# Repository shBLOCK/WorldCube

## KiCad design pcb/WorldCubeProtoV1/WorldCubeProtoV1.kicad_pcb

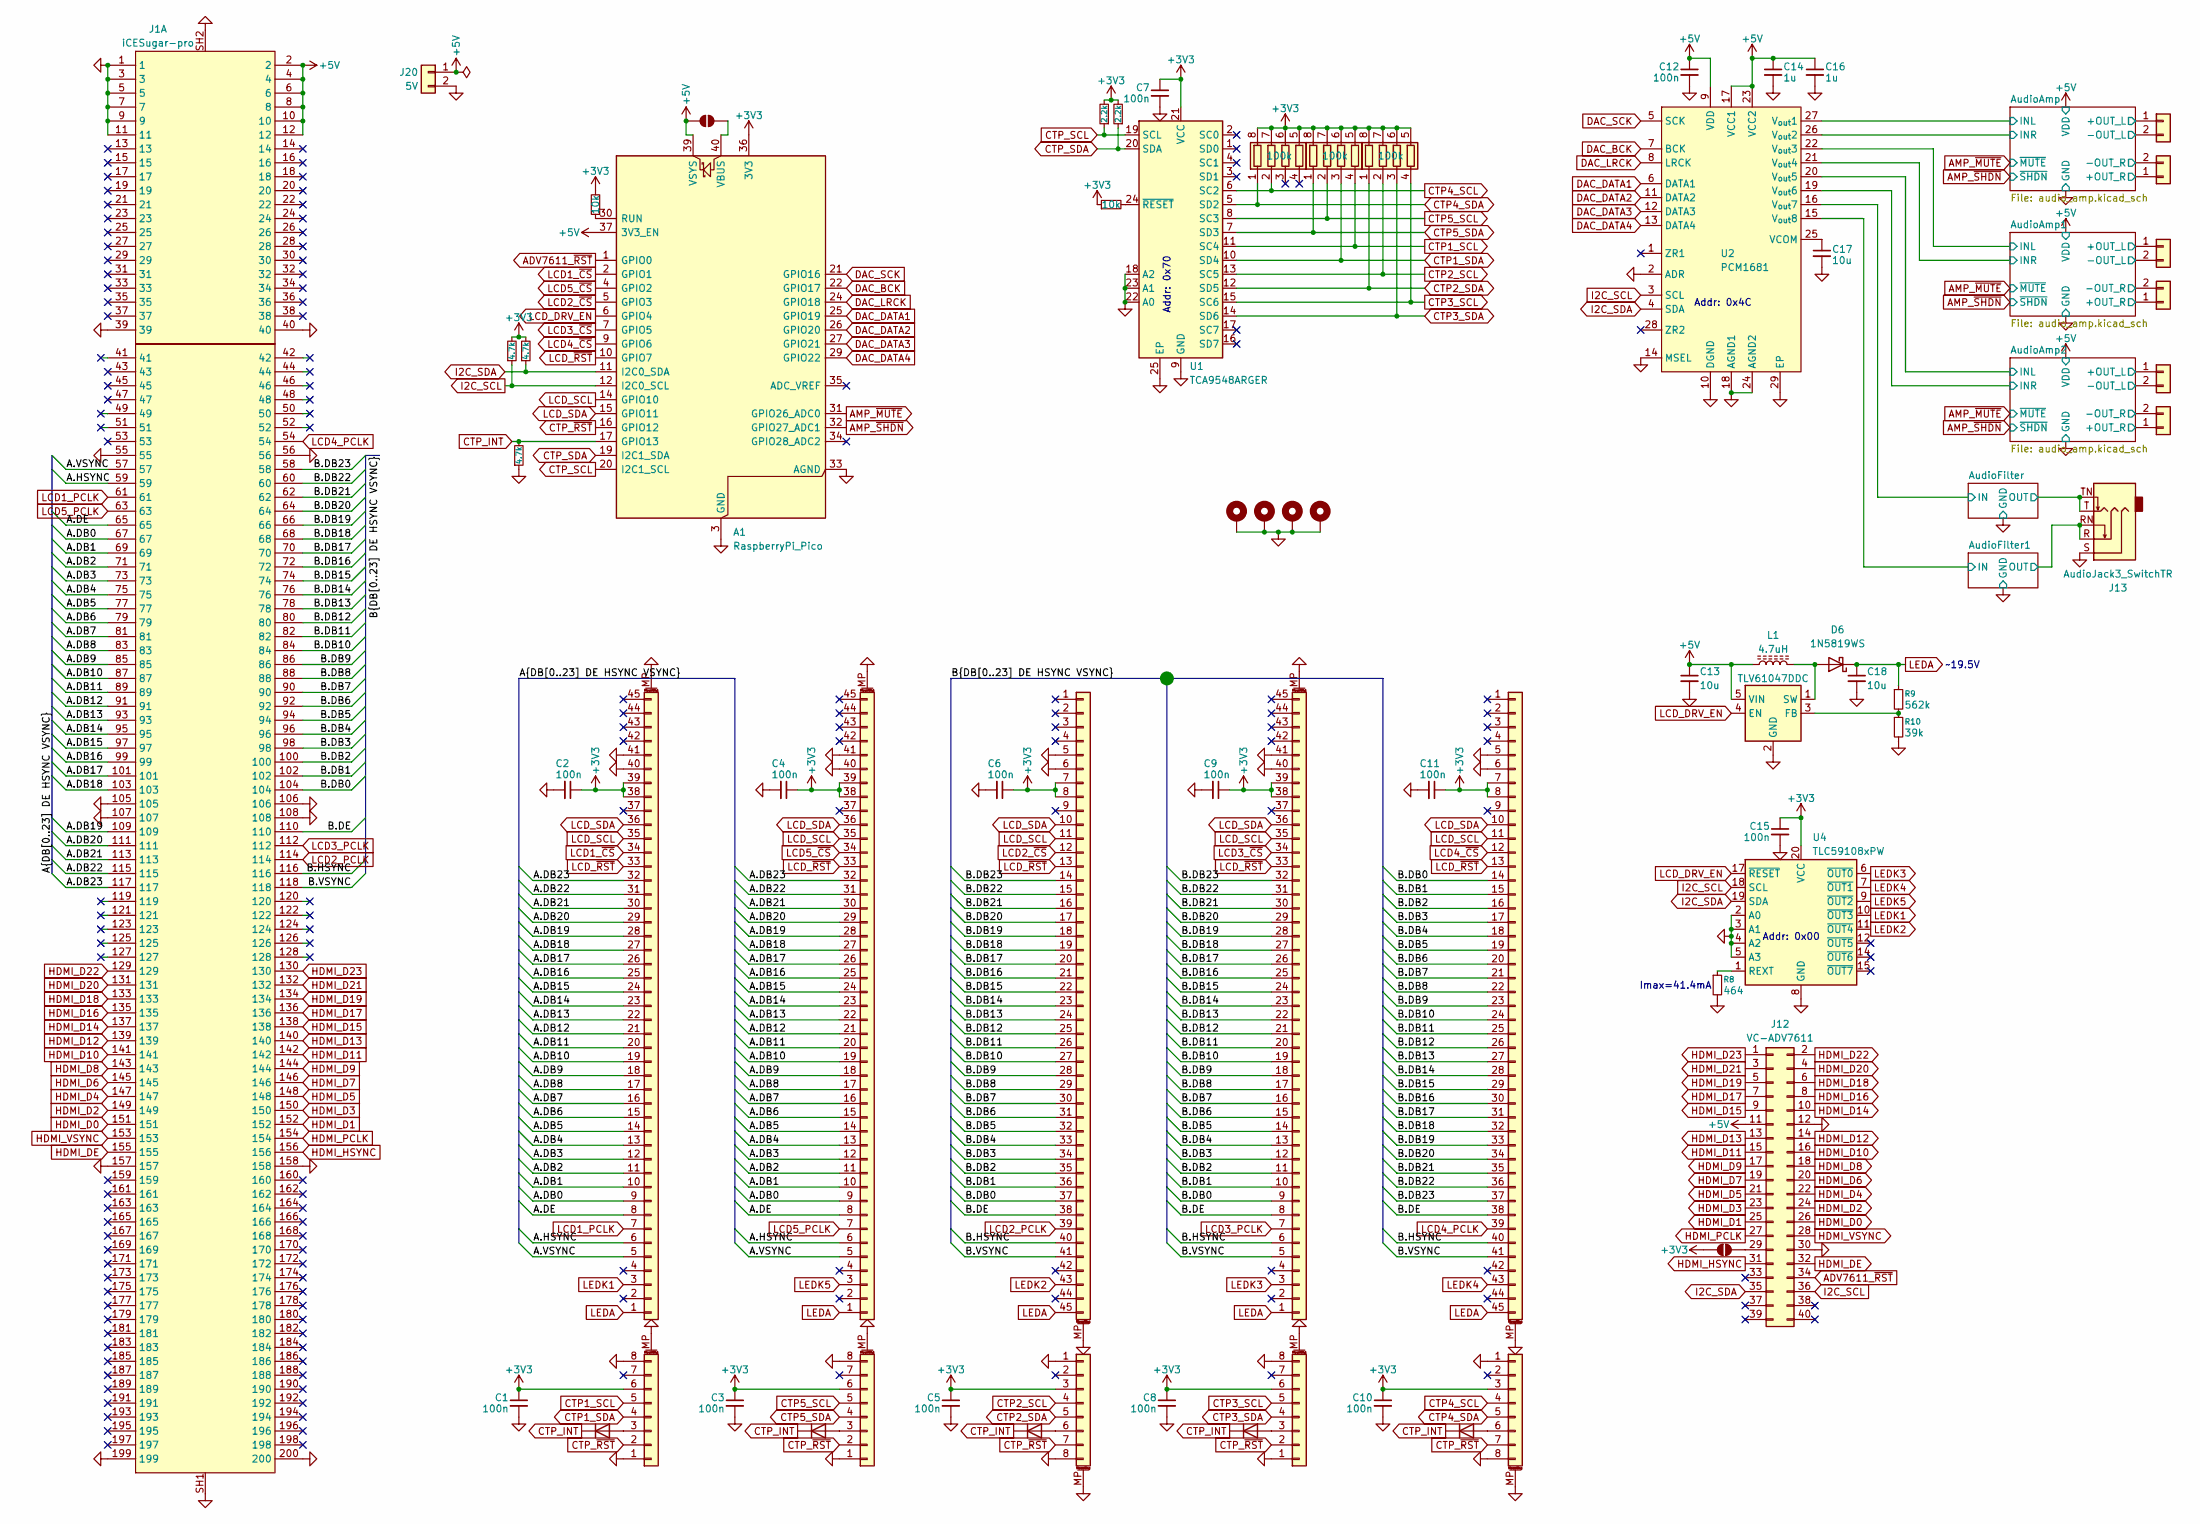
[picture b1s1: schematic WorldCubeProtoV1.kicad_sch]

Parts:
A1: RaspberryPi_Pico; RaspberryPi_Pico_Common_SMD; LCSC C42924268
C1, C2, C3, C4, C5, C6, C7, C8, C9, C10, C11, C12, C15: 100n; C_0603_1608Metric; LCSC C14663
C13, C18: 10u; C_0805_2012Metric; LCSC C2932476
C14, C16: 1u; C_0603_1608Metric; LCSC C15849
C17: 10u; C_0603_1608Metric; LCSC C19702
D1, D2, D3, D4, D5: 1N4148WT; D_SOD-523; LCSC C7420320
D6: 1N5819WS; D_SOD-323; LCSC C191023
H1, H2, H3, H4: MountingHole_Pad; MountingHole_3.2mm_M3_Pad
J1: iCESugar-pro; TE_1565917-4; LCSC C279171
J2, J4, J8: KD040WXFPD014; TE_4-1734839-5_1x45-1MP_P0.5mm_Horizontal; LCSC C53058
J3, J5, J9: KD040WXFPD014-C015C_CTP; TE_0-1734839-8_1x08-1MP_P0.5mm_Horizontal; LCSC C262555
J6, J10: KD040WXFPD014; TE_4-1734839-5_1x45-1MP_P0.5mm_Horizontal; LCSC C262649
J7, J11: KD040WXFPD014-C015C_CTP; TE_0-1734839-8_1x08-1MP_P0.5mm_Horizontal; LCSC C262581
J12: VC-ADV7611; PinHeader_2x20_P2.54mm_Vertical; LCSC C5224014
J13: AudioJack3_SwitchTR; Jack_3.5mm_CUI_SJ1-3515N_Horizontal; LCSC C145814
J14, J15, J16, J17, J18, J19: Conn_01x02; Molex_PicoBlade_53047-0210_1x02_P1.25mm_Vertical; LCSC C7430458
J20: 5V; JST_XH_B2B-XH-A_1x02_P2.50mm_Vertical; LCSC C158012
JP1, JP2: SolderJumper_2_Open; SolderJumper-2_P1.3mm_Open_RoundedPad1.0x1.5mm
L1: 4.7uH; L_Changjiang_FTC252010S; LCSC C5832360
R1, R6: 10k; R_0603_1608Metric; LCSC C25804
R2, R3, R4: 4.7k; R_0603_1608Metric; LCSC C23162
R5, R7: 2.2k; R_0603_1608Metric; LCSC C4190
R8: 464; R_0603_1608Metric; LCSC C5159701
R9: 562k; R_0603_1608Metric; LCSC C23205
R10: 39k; R_0603_1608Metric; LCSC C23153
RN1, RN2, RN3: 100k; R_Array_Convex_4x0603; LCSC C192933
U1: TCA9548ARGER; Texas_RGE0024C_VQFN-24-1EP_4x4mm_P0.5mm_EP2.1x2.1mm; LCSC C555456
U2: PCM1681; HTSSOP-28-1EP_4.4x9.7mm_P0.65mm_EP3.4x9.5mm_Mask2.4x6.17mm; LCSC C2667052
U3: TLV61047DDC; SOT-23-5; LCSC C44538408
U4: TLC59108xPW; TSSOP-20_4.4x6.5mm_P0.65mm; LCSC C130031

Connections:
+3V3: A1.36 (3V3), C1.1, C2.1, C3.1, C4.1, C5.1, C6.1, C7.1, C8.1, C9.1, C10.1, C11.1, C15.1, J2.38, J2.39, J3.6, J4.38, J4.39, J5.6, J6.7, J6.8, J7.3, J8.38, J8.39, J9.6, J10.7, J10.8, J11.3, JP2.1 (A), R1.2, R2.2, R3.2, R5.2, R6.1, R7.2, RN1.5 (R4.2), RN1.6 (R3.2), RN1.7 (R2.2), RN1.8 (R1.2), RN2.5 (R4.2), RN2.6 (R3.2), RN2.7 (R2.2), RN2.8 (R1.2), RN3.5 (R4.2), RN3.6 (R3.2), RN3.7 (R2.2), RN3.8 (R1.2), U1.21 (VCC), U4.20 (VCC)
+5V: A1.37 (3V3_EN), A1.39 (VSYS), C12.1, C13.1, C14.1, C16.1, J1.2, J1.4, J1.6, J1.8, J1.10, J1.12, J12.11, J20.1, JP1.1 (A), L1.1, U2.9 (VDD), U2.17 (VCC1), U2.23 (VCC2), U3.5 (VIN); also elsewhere on the board
/A.DB0: J1.67, J2.9, J4.9
/A.DB1: J1.69, J2.10, J4.10
/A.DB2: J1.71, J2.11, J4.11
/A.DB3: J1.73, J2.12, J4.12
/A.DB4: J1.75, J2.13, J4.13
/A.DB5: J1.77, J2.14, J4.14
/A.DB6: J1.79, J2.15, J4.15
/A.DB7: J1.81, J2.16, J4.16
/A.DB8: J1.83, J2.17, J4.17
/A.DB9: J1.85, J2.18, J4.18
/A.DB10: J1.87, J2.19, J4.19
/A.DB11: J1.89, J2.20, J4.20
/A.DB12: J1.91, J2.21, J4.21
/A.DB13: J1.93, J2.22, J4.22
/A.DB14: J1.95, J2.23, J4.23
/A.DB15: J1.97, J2.24, J4.24
/A.DB16: J1.99, J2.25, J4.25
/A.DB17: J1.101, J2.26, J4.26
/A.DB18: J1.103, J2.27, J4.27
/A.DB19: J1.109, J2.28, J4.28
/A.DB20: J1.111, J2.29, J4.29
/A.DB21: J1.113, J2.30, J4.30
/A.DB22: J1.115, J2.31, J4.31
/A.DB23: J1.117, J2.32, J4.32
/A.DE: J1.65, J2.8, J4.8
/A.HSYNC: J1.59, J2.6, J4.6
/A.VSYNC: J1.57, J2.5, J4.5
/AudioAmp1/+OUT_L: J16.1; also elsewhere on the board
/AudioAmp1/+OUT_R: J17.1; also elsewhere on the board
/AudioAmp1/-OUT_L: J16.2; also elsewhere on the board
/AudioAmp1/-OUT_R: J17.2; also elsewhere on the board
/AudioAmp1/INL: U2.22 (V_{out}3); also elsewhere on the board
/AudioAmp1/INR: U2.21 (V_{out}4); also elsewhere on the board
/AudioAmp2/+OUT_L: J18.1; also elsewhere on the board
/AudioAmp2/+OUT_R: J19.1; also elsewhere on the board
/AudioAmp2/-OUT_L: J18.2; also elsewhere on the board
/AudioAmp2/-OUT_R: J19.2; also elsewhere on the board
/AudioAmp2/INL: U2.20 (V_{out}5); also elsewhere on the board
/AudioAmp2/INR: U2.19 (V_{out}6); also elsewhere on the board
/AudioAmp/+OUT_L: J14.1; also elsewhere on the board
/AudioAmp/+OUT_R: J15.1; also elsewhere on the board
/AudioAmp/-OUT_L: J14.2; also elsewhere on the board
/AudioAmp/-OUT_R: J15.2; also elsewhere on the board
/AudioAmp/INL: U2.27 (V_{out}1); also elsewhere on the board
/AudioAmp/INR: U2.26 (V_{out}2); also elsewhere on the board
/AudioFilter1/IN: U2.15 (V_{out}8); also elsewhere on the board
/AudioFilter1/OUT: J13.R, J13.RN; also elsewhere on the board
/AudioFilter/IN: U2.16 (V_{out}7); also elsewhere on the board
/AudioFilter/OUT: J13.T, J13.TN; also elsewhere on the board
/B.DB0: J1.104, J6.37, J8.9, J10.14
/B.DB1: J1.102, J6.36, J8.10, J10.15
/B.DB2: J1.100, J6.35, J8.11, J10.16
/B.DB3: J1.98, J6.34, J8.12, J10.17
/B.DB4: J1.96, J6.33, J8.13, J10.18
/B.DB5: J1.94, J6.32, J8.14, J10.19
/B.DB6: J1.92, J6.31, J8.15, J10.20
/B.DB7: J1.90, J6.30, J8.16, J10.21
/B.DB8: J1.88, J6.29, J8.17, J10.22
/B.DB9: J1.86, J6.28, J8.18, J10.23
/B.DB10: J1.84, J6.27, J8.19, J10.24
/B.DB11: J1.82, J6.26, J8.20, J10.25
/B.DB12: J1.80, J6.25, J8.21, J10.26
/B.DB13: J1.78, J6.24, J8.22, J10.27
/B.DB14: J1.76, J6.23, J8.23, J10.28
/B.DB15: J1.74, J6.22, J8.24, J10.29
/B.DB16: J1.72, J6.21, J8.25, J10.30
/B.DB17: J1.70, J6.20, J8.26, J10.31
/B.DB18: J1.68, J6.19, J8.27, J10.32
/B.DB19: J1.66, J6.18, J8.28, J10.33
/B.DB20: J1.64, J6.17, J8.29, J10.34
/B.DB21: J1.62, J6.16, J8.30, J10.35
/B.DB22: J1.60, J6.15, J8.31, J10.36
/B.DB23: J1.58, J6.14, J8.32, J10.37
/B.DE: J1.110, J6.38, J8.8, J10.38
/B.HSYNC: J1.116, J6.40, J8.6, J10.40
/B.VSYNC: J1.118, J6.41, J8.5, J10.41
ADV7611_~RST: A1.1 (GPIO0), J12.34
AMP_~MUTE: A1.31 (GPIO26_ADC0); also elsewhere on the board
AMP_~SHDN: A1.32 (GPIO27_ADC1); also elsewhere on the board
CTP1_SCL: J3.5, RN2.4 (R4.1), U1.11 (SC4)
CTP1_SDA: J3.4, RN2.3 (R3.1), U1.10 (SD4)
CTP2_SCL: J7.4, RN3.2 (R2.1), U1.13 (SC5)
CTP2_SDA: J7.5, RN3.1 (R1.1), U1.12 (SD5)
CTP3_SCL: J9.5, RN3.4 (R4.1), U1.15 (SC6)
CTP3_SDA: J9.4, RN3.3 (R3.1), U1.14 (SD6)
CTP4_SCL: J11.4, RN1.2 (R2.1), U1.6 (SC2)
CTP4_SDA: J11.5, RN1.1 (R1.1), U1.5 (SD2)
CTP5_SCL: J5.5, RN2.2 (R2.1), U1.8 (SC3)
CTP5_SDA: J5.4, RN2.1 (R1.1), U1.7 (SD3)
CTP_INT: A1.17 (GPIO13), D1.1 (K), D2.1 (K), D3.1 (K), D4.1 (K), D5.1 (K), R4.2
CTP_SCL: A1.20 (I2C1_SCL), R5.1, U1.19 (SCL)
CTP_SDA: A1.19 (I2C1_SDA), R7.1, U1.20 (SDA)
CTP_~RST: A1.16 (GPIO12), J3.2, J5.2, J7.7, J9.2, J11.7
DAC_BCK: A1.22 (GPIO17), U2.7 (BCK)
DAC_DATA1: A1.25 (GPIO19), U2.6 (DATA1)
DAC_DATA2: A1.26 (GPIO20), U2.11 (DATA2)
DAC_DATA3: A1.27 (GPIO21), U2.12 (DATA3)
DAC_DATA4: A1.29 (GPIO22), U2.13 (DATA4)
DAC_LRCK: A1.24 (GPIO18), U2.8 (LRCK)
DAC_SCK: A1.21 (GPIO16), U2.5 (SCK)
GND: A1.3 (GND), A1.8 (GND), A1.13 (GND), A1.18 (GND), A1.23 (GND), A1.28 (GND), A1.33 (AGND), A1.38 (GND), C1.2, C2.2, C3.2, C4.2, C5.2, C6.2, C7.2, C8.2, C9.2, C10.2, C11.2, C12.2, C13.2, C14.2, C15.2, C16.2, C17.2, C18.2, H1.1, H2.1, H3.1, H4.1, J1.1, J1.3, J1.5, J1.7, J1.9, J1.11, J1.39, J1.40, J1.55, J1.56, J1.105, J1.106, J1.107, J1.108, J1.157, J1.158, J1.199, J1.200, J1.SH1, J1.SH2, J2.40, J2.41, J2.MP (MountPin), J3.1, J3.8, J3.MP (MountPin), J4.40, J4.41, J4.MP (MountPin), J5.1, J5.8, J5.MP (MountPin), J6.5, J6.6, J6.MP (MountPin), J7.1, J7.8, J7.MP (MountPin), J8.40, J8.41, J8.MP (MountPin), J9.1, J9.8, J9.MP (MountPin), J10.5, J10.6, J10.MP (MountPin), J11.1, J11.8, J11.MP (MountPin), J12.12, J12.30, J13.S, J20.2, R4.1, R8.2, R10.2, U1.9 (GND), U1.18 (A2), U1.22 (A0), U1.23 (A1), U1.25 (EP), U2.2 (ADR), U2.10 (DGND), U2.14 (MSEL), U2.18 (AGND1), U2.24 (AGND2), U2.29 (EP), U3.2 (GND), U4.2 (A0), U4.3 (A1), U4.4 (A2), U4.5 (A3), U4.8 (GND), U4.13 (GND), U4.16 (GND); also elsewhere on the board
HDMI_D0: J1.151, J12.26
HDMI_D1: J1.152, J12.25
HDMI_D2: J1.149, J12.24
HDMI_D3: J1.150, J12.23
HDMI_D4: J1.147, J12.22
HDMI_D5: J1.148, J12.21
HDMI_D6: J1.145, J12.20
HDMI_D7: J1.146, J12.19
HDMI_D8: J1.143, J12.18
HDMI_D9: J1.144, J12.17
HDMI_D10: J1.141, J12.16
HDMI_D11: J1.142, J12.15
HDMI_D12: J1.139, J12.14
HDMI_D13: J1.140, J12.13
HDMI_D14: J1.137, J12.10
HDMI_D15: J1.138, J12.9
HDMI_D16: J1.135, J12.8
HDMI_D17: J1.136, J12.7
HDMI_D18: J1.133, J12.6
HDMI_D19: J1.134, J12.5
HDMI_D20: J1.131, J12.4
HDMI_D21: J1.132, J12.3
HDMI_D22: J1.129, J12.2
HDMI_D23: J1.130, J12.1
HDMI_DE: J1.155, J12.32
HDMI_HSYNC: J1.156, J12.31
HDMI_PCLK: J1.154, J12.27
HDMI_VSYNC: J1.153, J12.28
I2C_SCL: A1.12 (I2C0_SCL), J12.36, R3.1, U2.3 (SCL), U4.18 (SCL)
I2C_SDA: A1.11 (I2C0_SDA), J12.35, R2.1, U2.4 (SDA), U4.19 (SDA)
LCD1_PCLK: J1.61, J2.7
LCD1_~CS: A1.2 (GPIO1), J2.34
LCD2_PCLK: J1.114, J6.39
LCD2_~CS: A1.5 (GPIO3), J6.12
LCD3_PCLK: J1.112, J8.7
LCD3_~CS: A1.7 (GPIO5), J8.34
LCD4_PCLK: J1.54, J10.39
LCD4_~CS: A1.9 (GPIO6), J10.12
LCD5_PCLK: J1.63, J4.7
LCD5_~CS: A1.4 (GPIO2), J4.34
LCD_DRV_EN: A1.6 (GPIO4), U3.4 (EN), U4.17 (~RESET)
LCD_SCL: A1.14 (GPIO10), J2.35, J4.35, J6.11, J8.35, J10.11
LCD_SDA: A1.15 (GPIO11), J2.36, J4.36, J6.10, J8.36, J10.10
LCD_~RST: A1.10 (GPIO7), J2.33, J4.33, J6.13, J8.33, J10.13
LEDA: C18.1, D6.1 (K), J2.1, J4.1, J6.45, J8.1, J10.45, R9.1
LEDK1: J2.3, U4.10 (~OUT3)
LEDK2: J6.43, U4.11 (~OUT4)
LEDK3: J8.3, U4.6 (~OUT0)
LEDK4: J10.43, U4.7 (~OUT1)
LEDK5: J4.3, U4.9 (~OUT2)
unnamed: A1.30 (RUN), R1.1
unnamed: A1.40 (VBUS), JP1.2 (B)
unnamed: D1.2 (A), J3.3
unnamed: D2.2 (A), J5.3
unnamed: D3.2 (A), J7.6
unnamed: D4.2 (A), J9.3
unnamed: D5.2 (A), J11.6
unnamed: D6.2 (A), L1.2, U3.1 (SW)
unnamed: J12.29, JP2.2 (B)
unnamed: R6.2, U1.24 (~RESET)
unnamed: C17.1, U2.25 (VCOM)
unnamed: R9.2, R10.1, U3.3 (FB)
unnamed: R8.1, U4.1 (REXT)

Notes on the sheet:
Addr: 0x4C
Imax=41.4mA
Addr: 0x70
Addr: 0x00
~19.5V

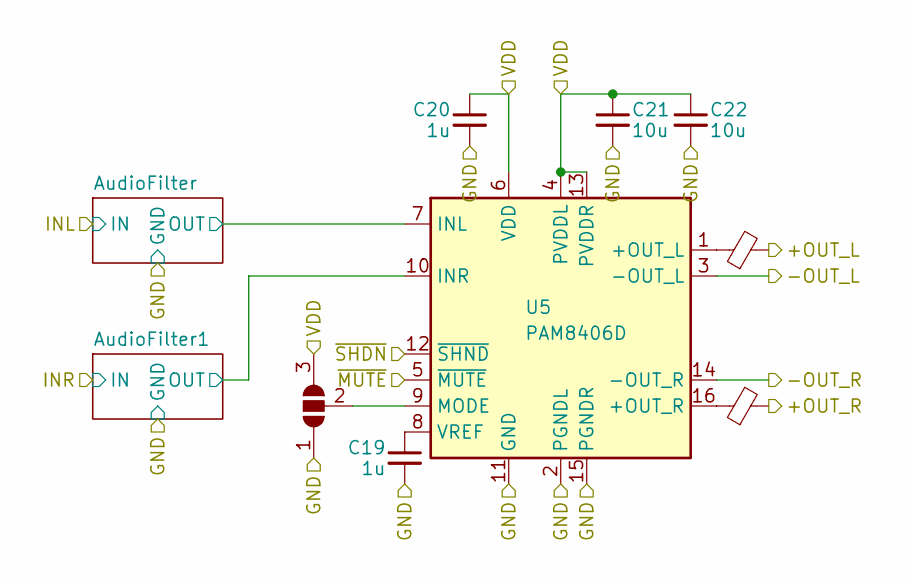
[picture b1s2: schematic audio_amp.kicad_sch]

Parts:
C19, C20: 1u; C_0603_1608Metric; LCSC C15849
C21, C22: 10u; C_0603_1608Metric; LCSC C19702
FB1, FB2: BLM21PG221SN1D; L_0805_2012Metric; LCSC C85840
JP3: AMP_MODE; SolderJumper-3_P1.3mm_Open_RoundedPad1.0x1.5mm
U5: PAM8406D; SOIC-16_3.9x9.9mm_P1.27mm; LCSC C86270

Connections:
+5V: C20.1, C21.1, C22.1, JP3.3 (B), U5.4 (PVDDL), U5.6 (VDD), U5.13 (PVDDR); also elsewhere on the board
/AudioAmp/+OUT_L: FB1.2; also elsewhere on the board
/AudioAmp/+OUT_R: FB2.2; also elsewhere on the board
/AudioAmp/-OUT_L: U5.3 (-OUT_L); also elsewhere on the board
/AudioAmp/-OUT_R: U5.14 (-OUT_R); also elsewhere on the board
/AudioAmp/AudioFilter1/OUT: U5.10 (INR); also elsewhere on the board
/AudioAmp/AudioFilter/OUT: U5.7 (INL); also elsewhere on the board
AMP_~MUTE: U5.5 (~MUTE); also elsewhere on the board
AMP_~SHDN: U5.12 (~SHND); also elsewhere on the board
GND: C19.2, C20.2, C21.2, C22.2, JP3.1 (A), U5.2 (PGNDL), U5.11 (GND), U5.15 (PGNDR); also elsewhere on the board
unnamed: JP3.2 (C), U5.9 (MODE)
unnamed: FB1.1, U5.1 (+OUT_L)
unnamed: FB2.1, U5.16 (+OUT_R)
unnamed: C19.1, U5.8 (VREF)

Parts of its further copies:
C23, C24, C27, C28: 1u; C_0603_1608Metric; LCSC C15849
C25, C26, C29, C30: 10u; C_0603_1608Metric; LCSC C19702
FB3, FB4, FB5, FB6: BLM21PG221SN1D; L_0805_2012Metric; LCSC C85840
JP4, JP5: AMP_MODE; SolderJumper-3_P1.3mm_Open_RoundedPad1.0x1.5mm
U6, U7: PAM8406D; SOIC-16_3.9x9.9mm_P1.27mm; LCSC C86270

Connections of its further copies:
+5V: C24.1, C25.1, C26.1, C28.1, C29.1, C30.1, JP4.3 (B), JP5.3 (B), U6.4 (PVDDL), U6.6 (VDD), U6.13 (PVDDR), U7.4 (PVDDL), U7.6 (VDD), U7.13 (PVDDR); also elsewhere on the board
/AudioAmp1/+OUT_L: FB3.2; also elsewhere on the board
/AudioAmp1/+OUT_R: FB4.2; also elsewhere on the board
/AudioAmp1/-OUT_L: U6.3 (-OUT_L); also elsewhere on the board
/AudioAmp1/-OUT_R: U6.14 (-OUT_R); also elsewhere on the board
/AudioAmp1/AudioFilter1/OUT: U6.10 (INR); also elsewhere on the board
/AudioAmp1/AudioFilter/OUT: U6.7 (INL); also elsewhere on the board
/AudioAmp2/+OUT_L: FB5.2; also elsewhere on the board
/AudioAmp2/+OUT_R: FB6.2; also elsewhere on the board
/AudioAmp2/-OUT_L: U7.3 (-OUT_L); also elsewhere on the board
/AudioAmp2/-OUT_R: U7.14 (-OUT_R); also elsewhere on the board
/AudioAmp2/AudioFilter1/OUT: U7.10 (INR); also elsewhere on the board
/AudioAmp2/AudioFilter/OUT: U7.7 (INL); also elsewhere on the board
AMP_~MUTE: U6.5 (~MUTE), U7.5 (~MUTE); also elsewhere on the board
AMP_~SHDN: U6.12 (~SHND), U7.12 (~SHND); also elsewhere on the board
GND: C23.2, C24.2, C25.2, C26.2, C27.2, C28.2, C29.2, C30.2, JP4.1 (A), JP5.1 (A), U6.2 (PGNDL), U6.11 (GND), U6.15 (PGNDR), U7.2 (PGNDL), U7.11 (GND), U7.15 (PGNDR); also elsewhere on the board
unnamed: JP4.2 (C), U6.9 (MODE)
unnamed: JP5.2 (C), U7.9 (MODE)
unnamed: FB3.1, U6.1 (+OUT_L)
unnamed: FB4.1, U6.16 (+OUT_R)
unnamed: C23.1, U6.8 (VREF)
unnamed: FB5.1, U7.1 (+OUT_L)
unnamed: FB6.1, U7.16 (+OUT_R)
unnamed: C27.1, U7.8 (VREF)

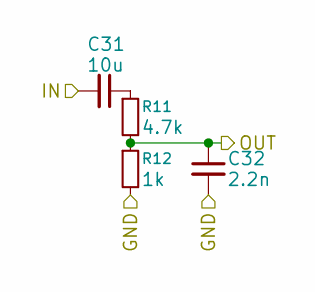
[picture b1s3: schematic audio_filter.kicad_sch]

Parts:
C31: 10u; C_0603_1608Metric; LCSC C19702
C32: 2.2n; C_0603_1608Metric; LCSC C1604
R11: 4.7k; R_0603_1608Metric; LCSC C23162
R12: 1k; R_0603_1608Metric; LCSC C21190

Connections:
/AudioAmp/AudioFilter/OUT: C32.1, R11.2, R12.1; also elsewhere on the board
/AudioAmp/INL: C31.2; also elsewhere on the board
GND: C32.2, R12.2; also elsewhere on the board
unnamed: C31.1, R11.1

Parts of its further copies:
C33, C35, C37, C39, C41, C43, C45: 10u; C_0603_1608Metric; LCSC C19702
C34, C36, C38, C40, C42, C44, C46: 2.2n; C_0603_1608Metric; LCSC C1604
R13, R15, R17, R19, R21, R23, R25: 4.7k; R_0603_1608Metric; LCSC C23162
R14, R16, R18, R20, R22, R24, R26: 1k; R_0603_1608Metric; LCSC C21190

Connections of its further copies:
/AudioAmp1/AudioFilter1/OUT: C40.1, R19.2, R20.1; also elsewhere on the board
/AudioAmp1/AudioFilter/OUT: C34.1, R13.2, R14.1; also elsewhere on the board
/AudioAmp1/INL: C33.2; also elsewhere on the board
/AudioAmp1/INR: C39.2; also elsewhere on the board
/AudioAmp2/AudioFilter1/OUT: C42.1, R21.2, R22.1; also elsewhere on the board
/AudioAmp2/AudioFilter/OUT: C36.1, R15.2, R16.1; also elsewhere on the board
/AudioAmp2/INL: C35.2; also elsewhere on the board
/AudioAmp2/INR: C41.2; also elsewhere on the board
/AudioAmp/AudioFilter1/OUT: C38.1, R17.2, R18.1; also elsewhere on the board
/AudioAmp/INR: C37.2; also elsewhere on the board
/AudioFilter1/IN: C45.2; also elsewhere on the board
/AudioFilter1/OUT: C46.1, R25.2, R26.1; also elsewhere on the board
/AudioFilter/IN: C43.2; also elsewhere on the board
/AudioFilter/OUT: C44.1, R23.2, R24.1; also elsewhere on the board
GND: C34.2, C36.2, C38.2, C40.2, C42.2, C44.2, C46.2, R14.2, R16.2, R18.2, R20.2, R22.2, R24.2, R26.2; also elsewhere on the board
unnamed: C33.1, R13.1
unnamed: C35.1, R15.1
unnamed: C37.1, R17.1
unnamed: C39.1, R19.1
unnamed: C41.1, R21.1
unnamed: C43.1, R23.1
unnamed: C45.1, R25.1

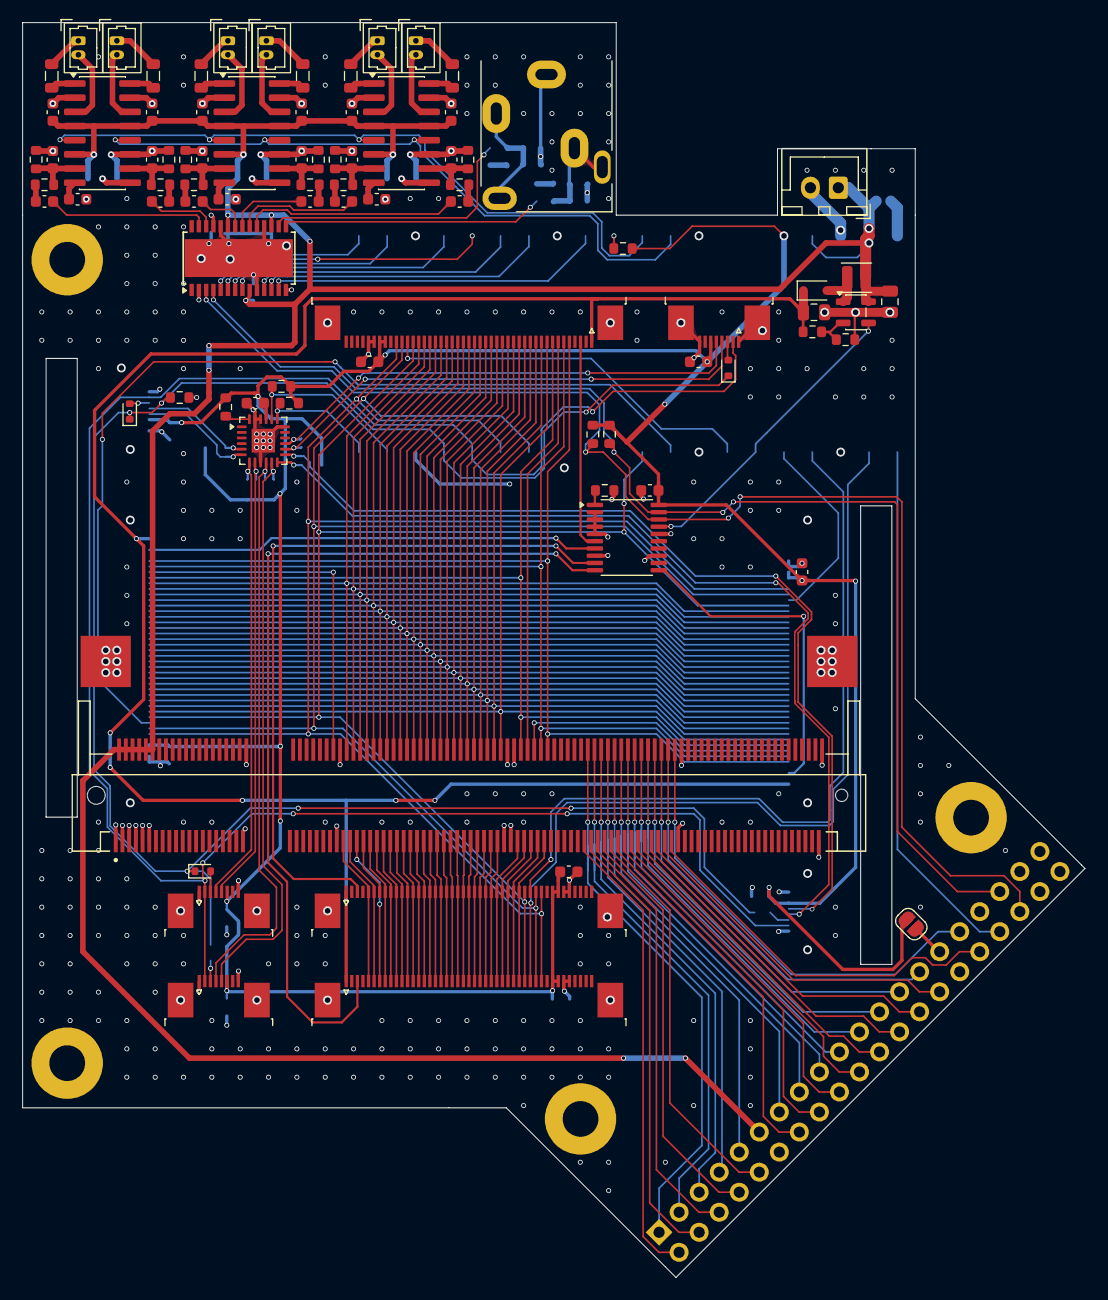
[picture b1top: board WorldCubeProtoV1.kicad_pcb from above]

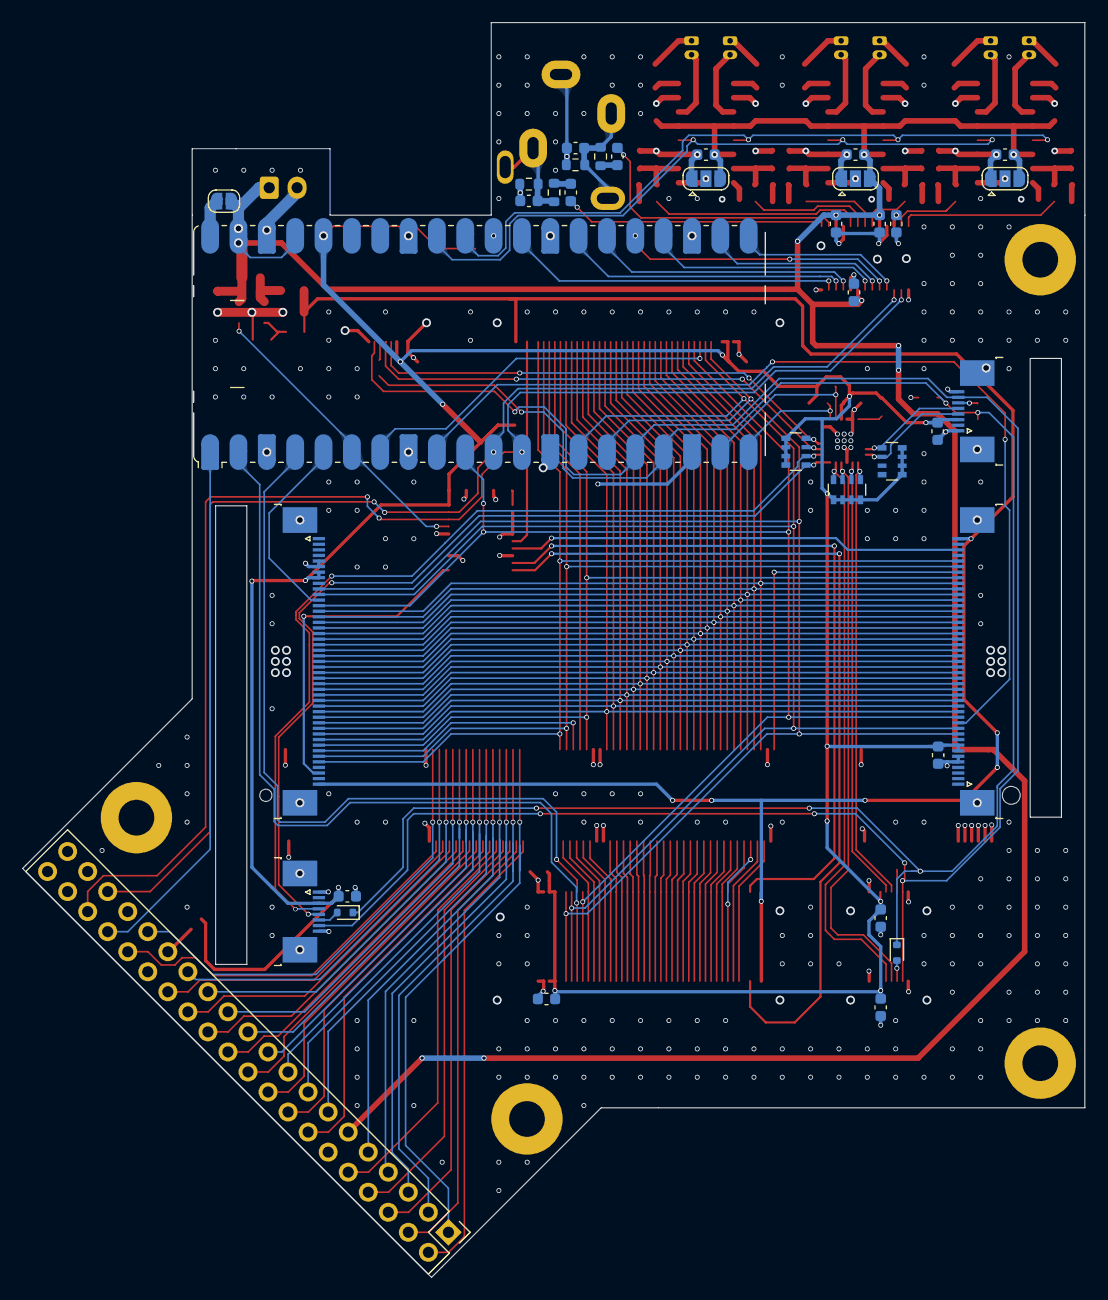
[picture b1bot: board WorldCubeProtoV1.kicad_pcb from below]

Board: 4 copper layers, 95.2 x 112.5 mm, 125 parts (36 on the bottom side), 192 nets.

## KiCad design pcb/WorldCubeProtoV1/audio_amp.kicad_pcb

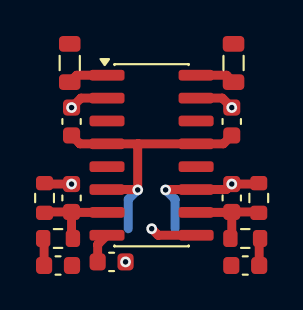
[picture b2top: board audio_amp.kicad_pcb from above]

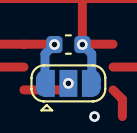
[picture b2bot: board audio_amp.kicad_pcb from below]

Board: 2 copper layers, 16 parts (2 on the bottom side), 10 nets.

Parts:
C1, C2: 1u; C_0603_1608Metric
C3, C4, C5, C7: 10u; C_0603_1608Metric
C6, C8: 2.2n; C_0603_1608Metric
FB1, FB2: BLM21PG221SN1D; L_0805_2012Metric
JP1: AMP_MODE; SolderJumper-3_P1.3mm_Open_RoundedPad1.0x1.5mm
R1, R3: 4.7k; R_0603_1608Metric
R2, R4: 1k; R_0603_1608Metric
U1: PAM8406D; SOIC-16_3.9x9.9mm_P1.27mm

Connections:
/AudioFilter1/OUT: C8.1, R3.2, R4.1, U1.10 (INR)
/AudioFilter/OUT: C6.1, R1.2, R2.1, U1.7 (INL)
/GND: C1.2, C2.2, C3.2, C4.2, C6.2, C8.2, JP1.1 (A), R2.2, R4.2, U1.2 (PGNDL), U1.11 (GND), U1.15 (PGNDR)
/VDD: C2.1, C3.1, C4.1, JP1.3 (B), U1.4 (PVDDL), U1.6 (VDD), U1.13 (PVDDR)
unnamed: C5.1, R1.1
unnamed: C7.1, R3.1
unnamed: JP1.2 (C), U1.9 (MODE)
unnamed: FB1.1, U1.1 (+OUT_L)
unnamed: FB2.1, U1.16 (+OUT_R)
unnamed: C1.1, U1.8 (VREF)

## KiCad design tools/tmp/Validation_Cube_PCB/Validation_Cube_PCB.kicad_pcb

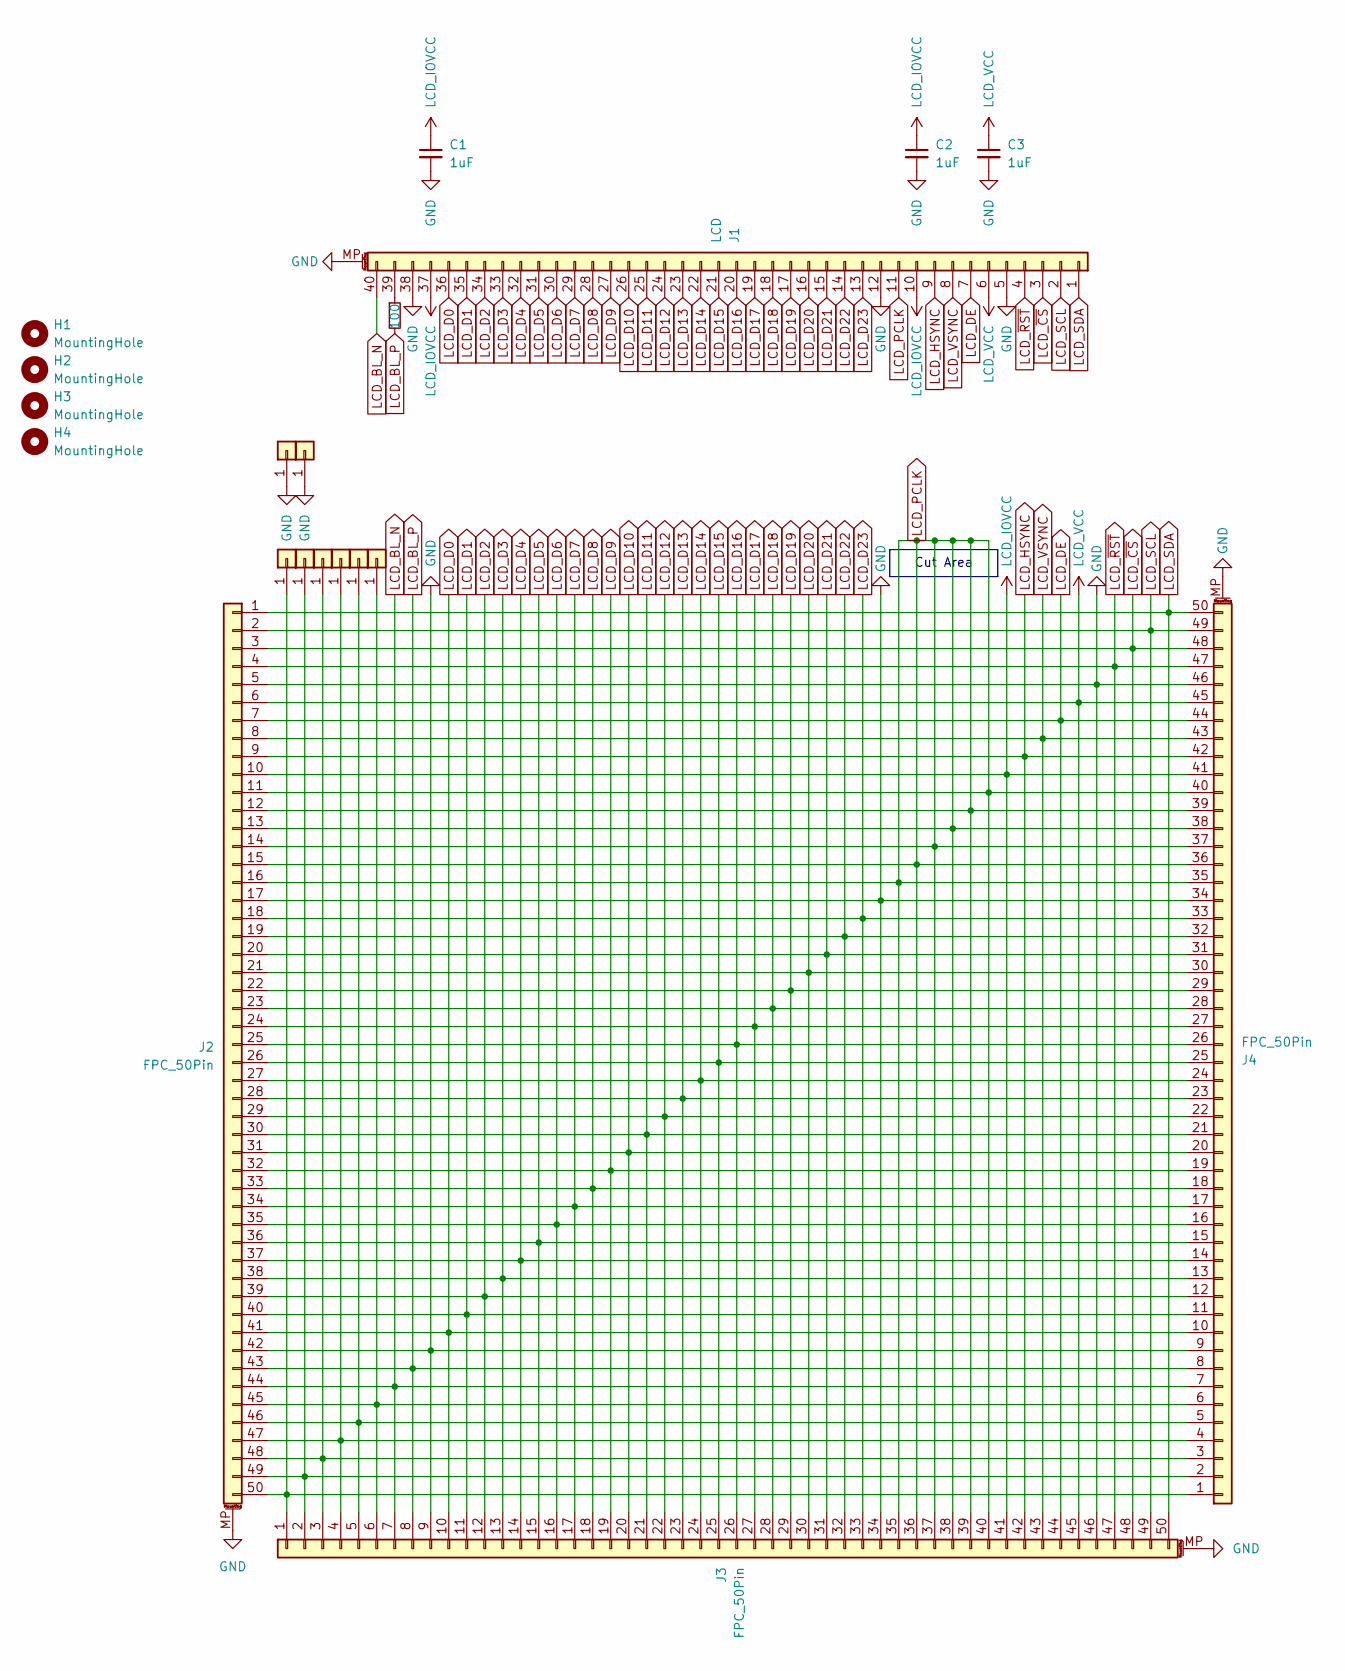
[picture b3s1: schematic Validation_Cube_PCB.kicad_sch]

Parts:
C1, C2, C3: 1uF; C_0603_1608Metric; LCSC C15849
H1, H2, H3, H4: MountingHole; MountingHole_3.2mm_M3
J1: LCD; TE_4-1734839-0_1x40-1MP_P0.5mm_Horizontal; LCSC C262648
J2, J3, J4: FPC_50Pin; TE_5-1734839-0_1x50-1MP_P0.5mm_Horizontal; LCSC C262650
J5, J6, J7, J8, J9, J10, J11, J12: Conn_01x01; SolderWire-0.1sqmm_1x01_D0.4mm_OD1mm
R1: 100; R_1206_3216Metric; LCSC C17901

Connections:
GND: C1.2, C2.2, C3.2, J1.5, J1.12, J1.38, J1.MP (MountPin), J2.5, J2.17, J2.42, J2.MP (MountPin), J3.9, J3.34, J3.46, J3.MP (MountPin), J4.9, J4.34, J4.46, J4.MP (MountPin), J11.1, J12.1
LCD_BL_N: J1.40, J2.44, J3.7, J4.7
LCD_BL_P: J2.43, J3.8, J4.8, R1.2
LCD_D0: J1.36, J2.41, J3.10, J4.10
LCD_D1: J1.35, J2.40, J3.11, J4.11
LCD_D2: J1.34, J2.39, J3.12, J4.12
LCD_D3: J1.33, J2.38, J3.13, J4.13
LCD_D4: J1.32, J2.37, J3.14, J4.14
LCD_D5: J1.31, J2.36, J3.15, J4.15
LCD_D6: J1.30, J2.35, J3.16, J4.16
LCD_D7: J1.29, J2.34, J3.17, J4.17
LCD_D8: J1.28, J2.33, J3.18, J4.18
LCD_D9: J1.27, J2.32, J3.19, J4.19
LCD_D10: J1.26, J2.31, J3.20, J4.20
LCD_D11: J1.25, J2.30, J3.21, J4.21
LCD_D12: J1.24, J2.29, J3.22, J4.22
LCD_D13: J1.23, J2.28, J3.23, J4.23
LCD_D14: J1.22, J2.27, J3.24, J4.24
LCD_D15: J1.21, J2.26, J3.25, J4.25
LCD_D16: J1.20, J2.25, J3.26, J4.26
LCD_D17: J1.19, J2.24, J3.27, J4.27
LCD_D18: J1.18, J2.23, J3.28, J4.28
LCD_D19: J1.17, J2.22, J3.29, J4.29
LCD_D20: J1.16, J2.21, J3.30, J4.30
LCD_D21: J1.15, J2.20, J3.31, J4.31
LCD_D22: J1.14, J2.19, J3.32, J4.32
LCD_D23: J1.13, J2.18, J3.33, J4.33
LCD_DE: J1.7, J2.7, J3.44, J4.44
LCD_HSYNC: J1.9, J2.9, J3.42, J4.42
LCD_IOVCC: C1.1, C2.1, J1.10, J1.37, J2.10, J3.41, J4.41
LCD_PCLK: J1.11, J2.11, J2.12, J2.13, J2.14, J2.15, J2.16, J3.35, J3.36, J3.37, J3.38, J3.39, J3.40, J4.35, J4.36, J4.37, J4.38, J4.39, J4.40
LCD_SCL: J1.2, J2.2, J3.49, J4.49
LCD_SDA: J1.1, J2.1, J3.50, J4.50
LCD_VCC: C3.1, J1.6, J2.6, J3.45, J4.45
LCD_VSYNC: J1.8, J2.8, J3.43, J4.43
LCD_~CS: J1.3, J2.3, J3.48, J4.48
LCD_~RST: J1.4, J2.4, J3.47, J4.47
unnamed: J1.39, R1.1
unnamed: J2.46, J3.5, J4.5, J9.1
unnamed: J2.47, J3.4, J4.4, J8.1
unnamed: J2.48, J3.3, J4.3, J7.1
unnamed: J2.49, J3.2, J4.2, J6.1
unnamed: J2.50, J3.1, J4.1, J5.1
unnamed: J2.45, J3.6, J4.6, J10.1

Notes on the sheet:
Cut Area

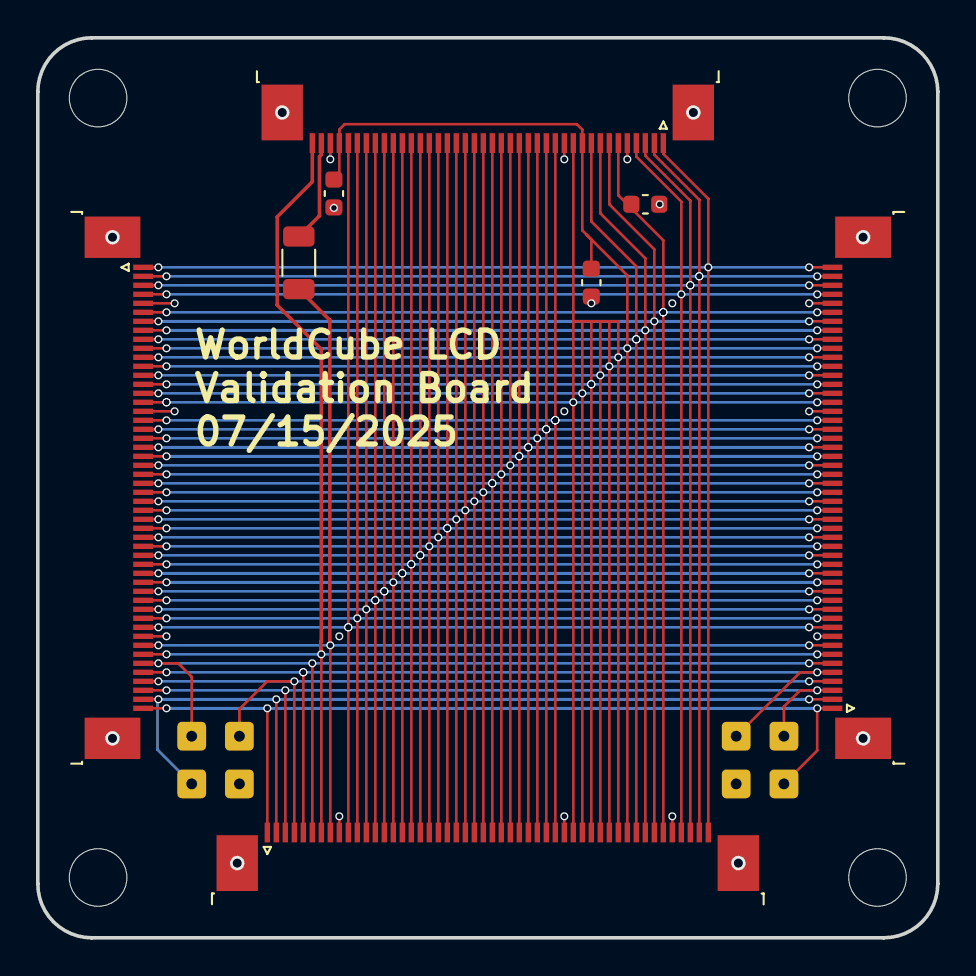
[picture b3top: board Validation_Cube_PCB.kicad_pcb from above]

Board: 4 copper layers, 50.0 x 50.0 mm, 20 parts (0 on the bottom side), 44 nets.
